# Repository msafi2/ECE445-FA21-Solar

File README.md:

# ECE445-FA21-Solar
GitHub Repository for UIUC ECE 445:Senior Design Laboratory Team in the Fall 2021 term comprised of Nikhil Mathew Sebastian (nikhils4), Sydney Li (sydneyl3), and Maram Safi (msafi2)

This repository contains all the source code for the Senior Design Lab project of this team, all relevant team project documentation, as well as team members' individual Lab Notebook entries. 

The project this team has undertaken is the **'Advanced Interface Box for Solar Panels'** project sponsored and advised for by Professor Arijit Banerjee.

## Team
1. Nikhil Mathew Sebastian [nikhils4]
2. Sydney Li [sydneyl3]
3. Maram Safi [msafi2]

## Problem
There are 60 solar panels on top of the ECEB building, currently being used for research, which are not producing any power as of now and can potentially be integrated into the power grid. Additionally, they are not adequately monitored at the moment and this poses a large hazard, especially considering there are no protection interfaces between the panels and their connections to the power inverter.

We want to design a smart interface box for these panels to allow for large-scale system behavior and output monitoring, as well as to support panel up-keep, to prevent any potential disasters like fires while also opening the possibility of future integration of these solar panels into other avenues. In previous semesters (FA19), a team of students were able to create an interface which was able to display a single panel's voltage and current, but the solution could not be scaled up to interface with multiple panels as is required. This previous solution attempt also now gives us a constrained size which we must utilize to communicate with multiple of these research solar panels.

## Solution Overview
Our solution to monitoring and maintaining the research solar panels is a smart interface box that will interface with multiple solar panels to produce a single wireless gateway of panel information that feeds into a visually attractive Research Hub for observation and access to research panel data.

The system will be powered from an isolated power supply. The power generated by each monitored solar panel will run through our smart interface box, giving us the ability to detect overvoltage and overcurrent conditions and disconnect individual panels if necessary to prevent hazardous situations. Other features of the box will include reconfigurable tapping to allow users to determine which solar panels themselves are being observed. We will also provide the possibility of manual configuration of solar panels through a wireless interface, allowing users to configure and monitor the solar panel remotely through a server/PC. Finally, LEDs will be used on the box to indicate the dynamic status of panels as well as the interface. As a fail-safe for remote management of the interface being unavailable, the configuration of the interface can also be controlled manually via onboard switches.

## Solution Components

* Switching Subsystem - Contains the ability to reconfigure which sections of the solar panel are being displayed to the wireless interface
* Manual Switches - For manual configuration of the interface box in which the wireless service access may be unavailable. The switches on the interface box can configure the solar panels and will be mounted on the enclosure. Most likely done through combinational or sequential logic depending on how much functionality we can implement
* LED Display - Displays the current status of information gathered from the panels and distinguishes whether the interface box is active or whether the wireless communication is accessible at the moment.
* Thermocouples - Measuring the temperature of the panels in a parallel manner so that a collective combination of data from different panels can be displayed.
* Microcontroller - The main processor for our interface box which has functionality such as being able to communicate the data received from the solar panels, shut down its 12V operations or limit any protection from overvoltage/current, and to determine areas in which certain panels may be overheating. Contains an electrical monitoring system to measure the voltage and current of the panels. We plan on displaying additional data beyond that which may include detailed waveforms and power calculations to our display system.
* Wireless Microchip - Utilizing a microchip to bring about wifi functionality to push data at high speeds from the interface box to the research hub
* Wireless sensor network - In order to scale up the project to have our microprocessor communicate with multiple solar panels, there needs to be a wireless node network. We cannot strictly rely on wiring which communicates one panel's information, instead having a range of sensor nodes spatially dispersed to monitor and record the conditions of each individual solar panel which help bring in collective data to our display.
* Remote Configuration Portal - An external system will be set-up with two-way communication with the box’s wireless network capabilities to allow for easy managing of the solar panels. Only authorized ECEB personnel will have access to this portal and it is intended for internal use, so the interface will be secured as such. The focus will be less the visualization of the data and more on porting the in-box button and switch capabilities to a remote setting for usage. Relevant data can be stored in a database, and a python-based framework will be able to extract and transmit commands, while JavaScript/Java can also be used to build up the framework. REST API can be utilized for the back-and-forth communication stream.
* Visual Display System - An external system that receives panel-specific data output through the Wireless Interface, and then stores the information in a database for display. Once again, a python-based framework will be able to extract, transmit commands, and display the data, while JavaScript/Java can also be used to build up the framework. REST API can also be used for receiving data. A web-based visualization of the data, with a focus on aesthetics, can then be provided for public display as well as monitoring. Both the database and the GUI will be secured to only allow authorized ECEB personnel to control the data.

## Criterion for Success

1. With a focus on scaling up to meet the requirements of the solar panels available, we need to be able to interface with at least 10 research solar panels to be successful
2. Interfacing with a solar panel successfully encompasses accurately monitoring its voltage, current, power output, and temperature while simultaneously reporting this data to an external server. (Higher functionality may include satellite imagery or different interpretations of the data received to determine the power usage during different times throughout the day.)
3. Remote Wireless Access towards the panels for the authorized ECEB personnel will be successful when it allows for these personnel to configure the solar panels from an external system
4. A successful interface will also provide a Wireless one-way communication to a visual “Hub” for scaled panel monitoring, providing aesthetic visualizations of panel data for observation as well as for general viewing
5. A successful prototype will also maintain the ability to manually control the interface box with in-box buttons and switches as a fail-safe

Our final goal is to have an easy-to-use interface supported by our smart box that allows for accurate and convenient monitoring and up-keep of multiple ECEB research solar panels. We aim to have a prototype that can easily be scaled to meet the entire requirement of available solar panels, and in the end be successfully deployed in the ECEB!

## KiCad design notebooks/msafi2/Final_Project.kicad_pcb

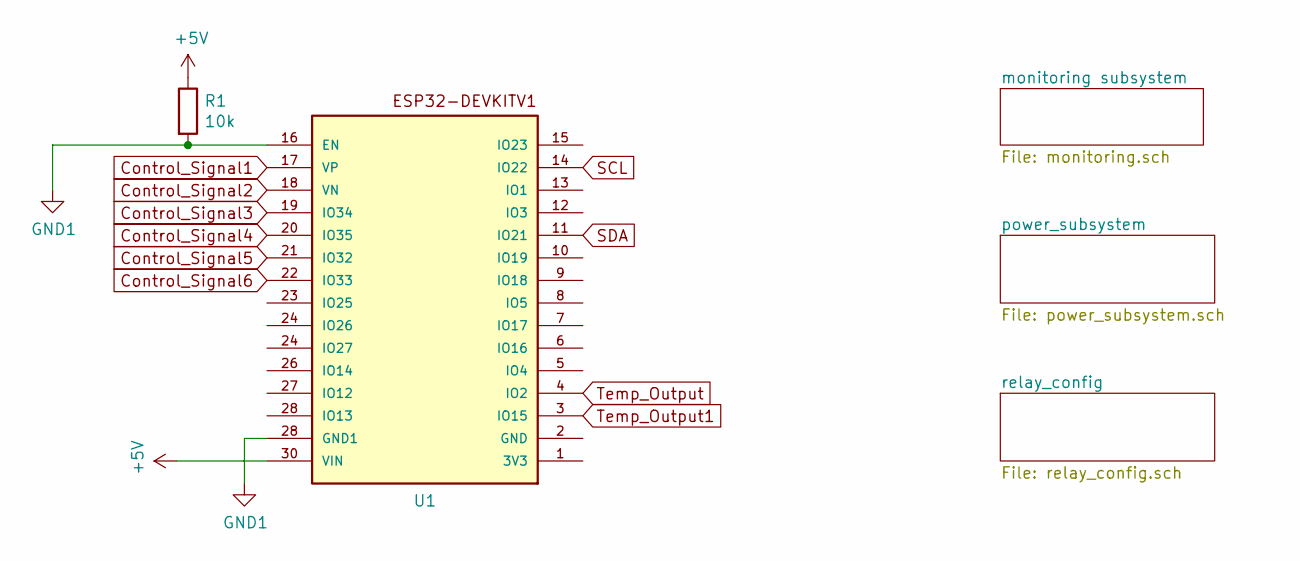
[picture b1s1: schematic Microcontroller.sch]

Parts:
R1: 10k; R_0603_1608Metric_Pad0.98x0.95mm_HandSolder
U1: ESP32DEVKITV1; ESP32-DEVKITV1

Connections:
+5V: R1.1, U1.30 (VIN); also elsewhere on the board
Control_Signal1: U1.17 (VP); also elsewhere on the board
Control_Signal2: U1.18 (VN); also elsewhere on the board
Control_Signal3: U1.19 (IO34); also elsewhere on the board
Control_Signal4: U1.20 (IO35); also elsewhere on the board
Control_Signal5: U1.21 (IO32); also elsewhere on the board
Control_Signal6: U1.22 (IO33); also elsewhere on the board
Current_output_voltage: U1.5 (IO4); also elsewhere on the board
GND1: R1.2, U1.16 (EN), U1.28 (GND1); also elsewhere on the board
SCL: U1.14 (IO22); also elsewhere on the board
SDA: U1.11 (IO21); also elsewhere on the board
Temp_Output: U1.4 (IO2); also elsewhere on the board
Temp_Output1: U1.3 (IO15); also elsewhere on the board

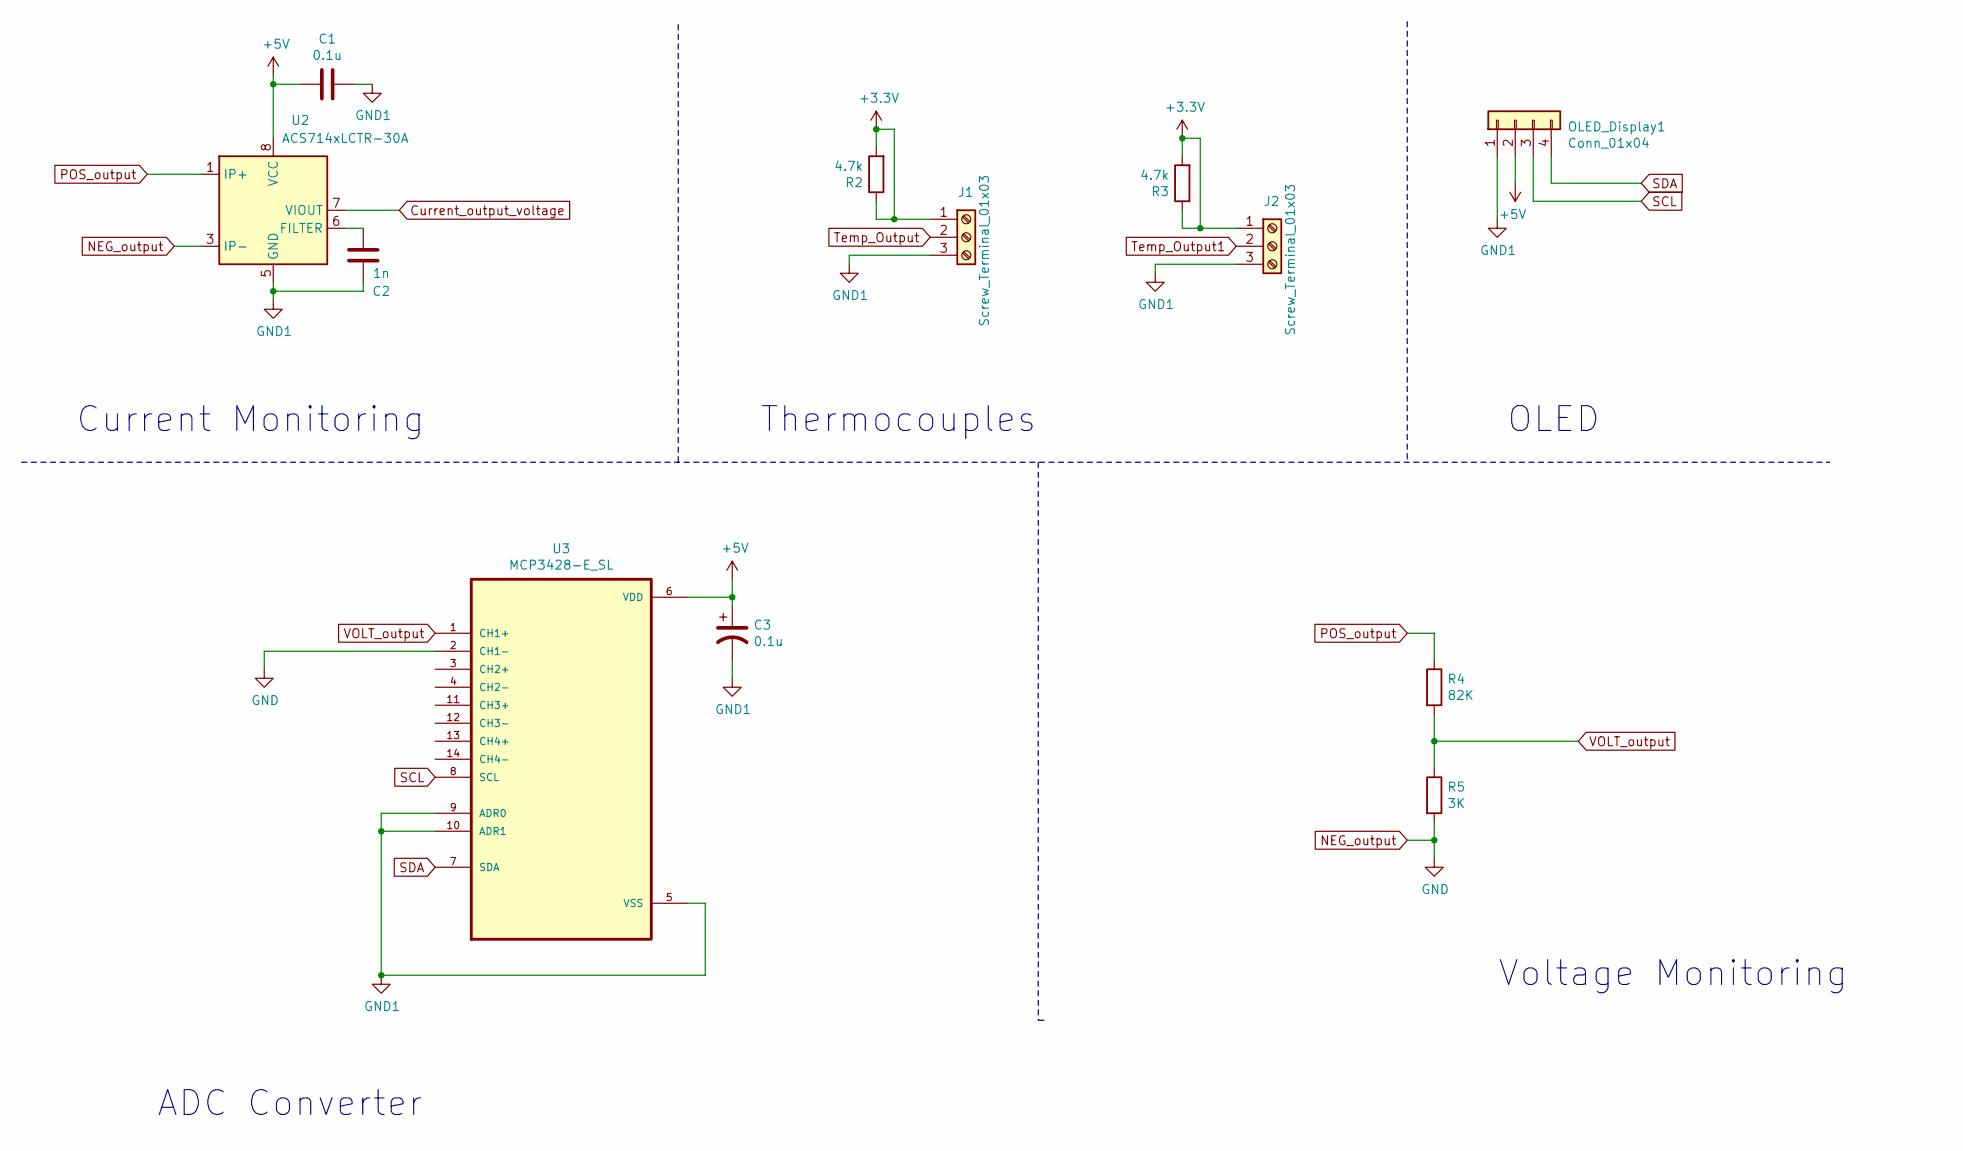
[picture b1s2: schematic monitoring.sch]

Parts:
C1, C3: 0.1u; C_0805_2012Metric_Pad1.18x1.45mm_HandSolder
C2: 1n; C_0805_2012Metric_Pad1.18x1.45mm_HandSolder
J1, J2: Screw_Terminal_01x03; 2828373
OLED_Display1: Conn_01x04; OLEDdisplay
R2, R3: 4.7k; R_0603_1608Metric_Pad0.98x0.95mm_HandSolder
R4: 82K; R_0603_1608Metric_Pad0.98x0.95mm_HandSolder
R5: 3K; R_0603_1608Metric_Pad0.98x0.95mm_HandSolder
U2: ACS714xLCTR-30A; SOIC-8_3.9x4.9mm_P1.27mm
U3: MCP3428-E_SL; SOIC127P600X175-14N

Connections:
+3V3: J1.1, J2.1, R2.1, R2.2, R3.1, R3.2; also elsewhere on the board
+5V: C1.2, C3.1, OLED_Display1.2, U2.8 (VCC), U3.6 (VDD); also elsewhere on the board
Current_output_voltage: U2.7 (VIOUT); also elsewhere on the board
GND1: C1.1, C2.1, C3.2, J1.3, J2.3, OLED_Display1.1, U2.5 (GND), U3.5 (VSS), U3.9 (ADR0), U3.10 (ADR1); also elsewhere on the board
unnamed: C2.2, U2.6 (FILTER)
POS_output: R4.1, U2.1 (IP+), U2.2 (IP+); also elsewhere on the board
SCL: OLED_Display1.3, U3.8 (SCL); also elsewhere on the board
SDA: OLED_Display1.4, U3.7 (SDA); also elsewhere on the board
Temp_Output: J1.2; also elsewhere on the board
Temp_Output1: J2.2; also elsewhere on the board
VOLT_output: R4.2, R5.1, U3.1 (CH1+)

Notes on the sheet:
Current Monitoring
Thermocouples
OLED
ADC Converter
Voltage Monitoring

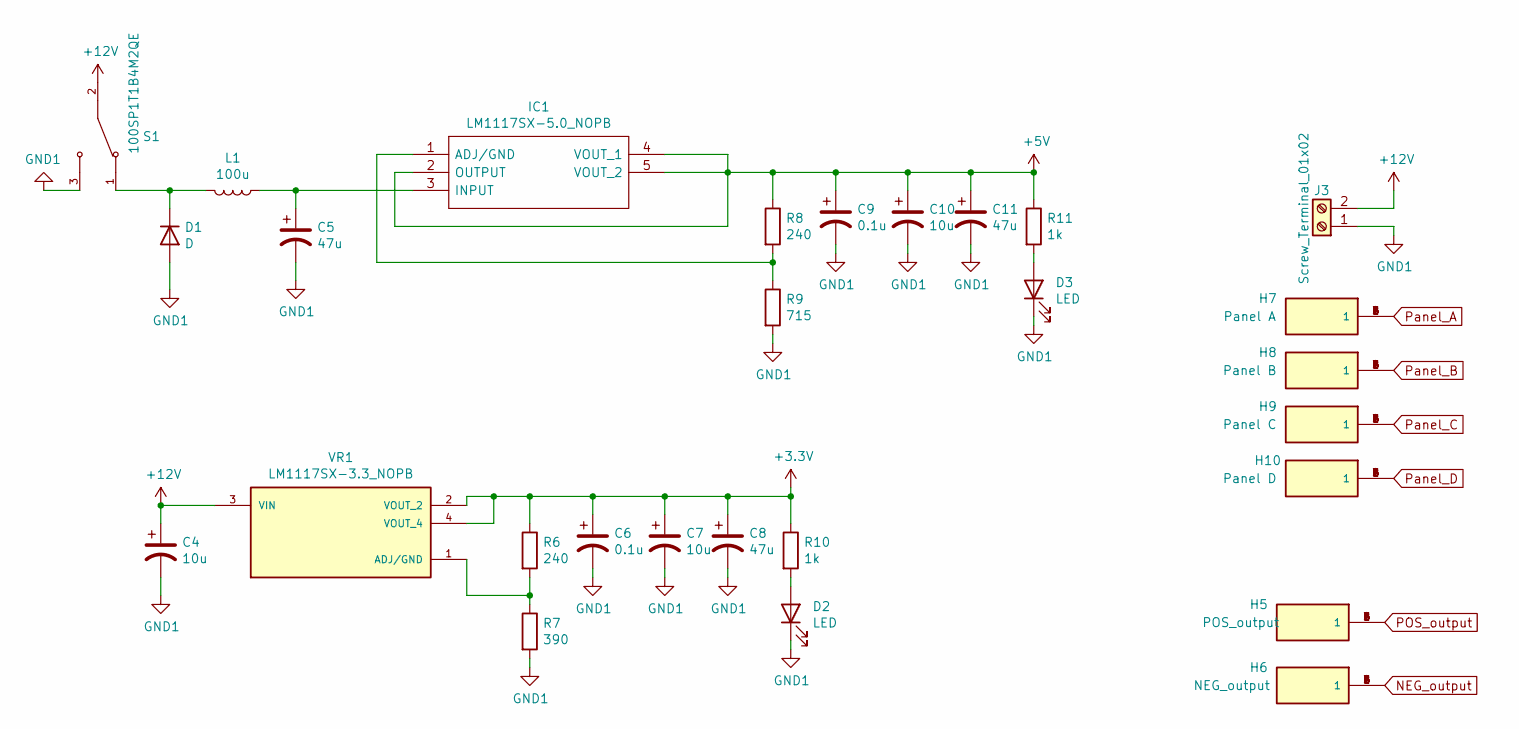
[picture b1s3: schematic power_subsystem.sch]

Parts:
C4, C7, C10: 10u; C_0805_2012Metric_Pad1.18x1.45mm_HandSolder
C5, C8, C11: 47u; CP_Elec_6.3x5.8
C6, C9: 0.1u; C_0805_2012Metric_Pad1.18x1.45mm_HandSolder
D1: D; D_0603_1608Metric_Pad1.05x0.95mm_HandSolder
D2, D3: LED; D_0603_1608Metric_Pad1.05x0.95mm_HandSolder
H5: POS_output; KEYSTONE_8197; PARTREV C
H6: NEG_output; KEYSTONE_8197; PARTREV C
H7: Panel A; KEYSTONE_8197; PARTREV C
H8: Panel B; KEYSTONE_8197; PARTREV C
H9: Panel C; KEYSTONE_8197; PARTREV C
H10: Panel D; KEYSTONE_8197; PARTREV C
IC1: LM1117SX-5.0_NOPB; LM1117SX50NOPB; Manufacturer_Part_Number LM1117SX-5.0/NOPB; Mouser Part Number 926-LM1117SX50NOPB
J3: Screw_Terminal_01x02; 2828372
L1: 100u; L_0603_1608Metric_Pad1.05x0.95mm_HandSolder
R6, R8: 240; R_0603_1608Metric_Pad0.98x0.95mm_HandSolder
R7: 390; R_0603_1608Metric_Pad0.98x0.95mm_HandSolder
R9: 715; R_0603_1608Metric_Pad0.98x0.95mm_HandSolder
R10, R11: 1k; R_0603_1608Metric_Pad0.98x0.95mm_HandSolder
S1: 100SP1T1B4M2QE; SW_100SP1T1B4M2QE; PARTREV E
VR1: LM1117SX-3.3_NOPB; TO254P1435X464-4N; PARTREV O

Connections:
+3V3: C6.1, C7.1, C8.1, R6.1, R10.1, VR1.2 (VOUT_2), VR1.4 (VOUT_4); also elsewhere on the board
+5V: C9.1, C10.1, C11.1, IC1.2 (OUTPUT), IC1.4 (VOUT_1), IC1.5 (VOUT_2), R8.1, R11.1; also elsewhere on the board
+12V: C4.1, J3.2, S1.2, VR1.3 (VIN)
GND1: C4.2, C5.2, C6.2, C7.2, C8.2, C9.2, C10.2, C11.2, D1.2 (A), D2.1 (K), D3.1 (K), J3.1, R7.2, R9.2, S1.3; also elsewhere on the board
unnamed: C5.1, IC1.3 (INPUT), L1.1
unnamed: D1.1 (K), L1.2, S1.1
unnamed: D2.2 (A), R10.2
unnamed: D3.2 (A), R11.2
unnamed: IC1.1 (ADJ/GND), R8.2, R9.1
unnamed: R6.2, R7.1, VR1.1 (ADJ/GND)
POS_output: H5.1, H5.2, H5.3, H5.4, H5.5, H5.6; also elsewhere on the board
Panel_A: H7.1, H7.2, H7.3, H7.4, H7.5, H7.6; also elsewhere on the board
Panel_B: H8.1, H8.2, H8.3, H8.4, H8.5, H8.6; also elsewhere on the board
Panel_C: H9.1, H9.2, H9.3, H9.4, H9.5, H9.6; also elsewhere on the board
Panel_D: H10.1, H10.2, H10.3, H10.4, H10.5, H10.6; also elsewhere on the board

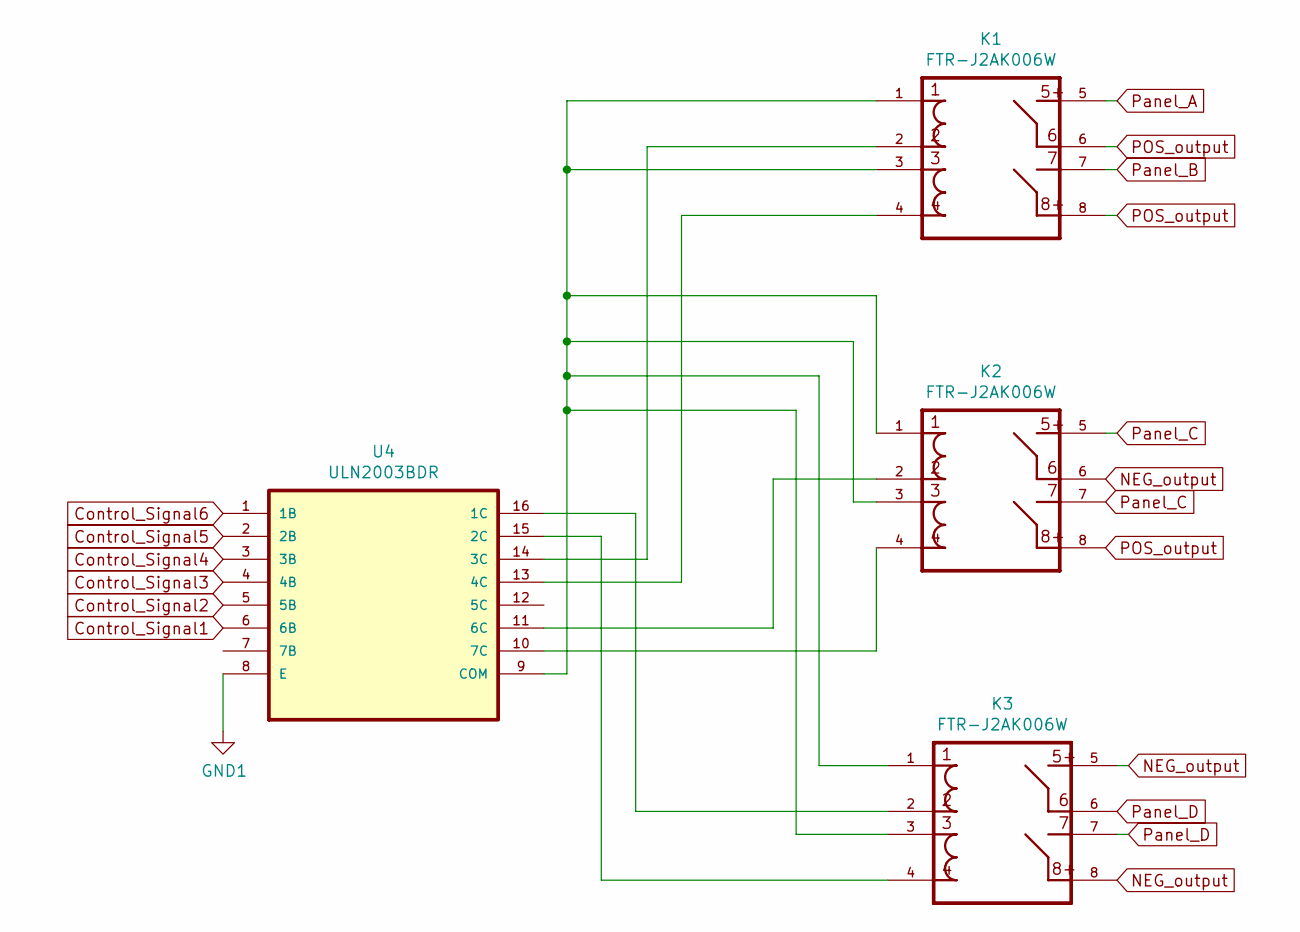
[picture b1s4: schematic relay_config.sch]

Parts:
K1, K2, K3: FTR-J2AK006W; RELAY_FTR-J2AK006W
U4: ULN2003BDR; SOIC127P600X175-16N

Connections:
Control_Signal1: U4.6 (6B); also elsewhere on the board
Control_Signal2: U4.5 (5B); also elsewhere on the board
Control_Signal3: U4.4 (4B); also elsewhere on the board
Control_Signal4: U4.3 (3B); also elsewhere on the board
Control_Signal5: U4.2 (2B); also elsewhere on the board
Control_Signal6: U4.1 (1B); also elsewhere on the board
GND1: U4.8 (E); also elsewhere on the board
unnamed: K1.1, K1.3, K2.1, K2.3, K3.1, K3.3, U4.9 (COM)
unnamed: K1.2, U4.14 (3C)
unnamed: K1.4, U4.13 (4C)
unnamed: K2.2, U4.11 (6C)
unnamed: K2.4, U4.10 (7C)
unnamed: K3.2, U4.16 (1C)
unnamed: K3.4, U4.15 (2C)
POS_output: K1.6, K1.8, K2.8; also elsewhere on the board
Panel_A: K1.5; also elsewhere on the board
Panel_B: K1.7; also elsewhere on the board
Panel_C: K2.5, K2.7; also elsewhere on the board
Panel_D: K3.6, K3.7; also elsewhere on the board

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
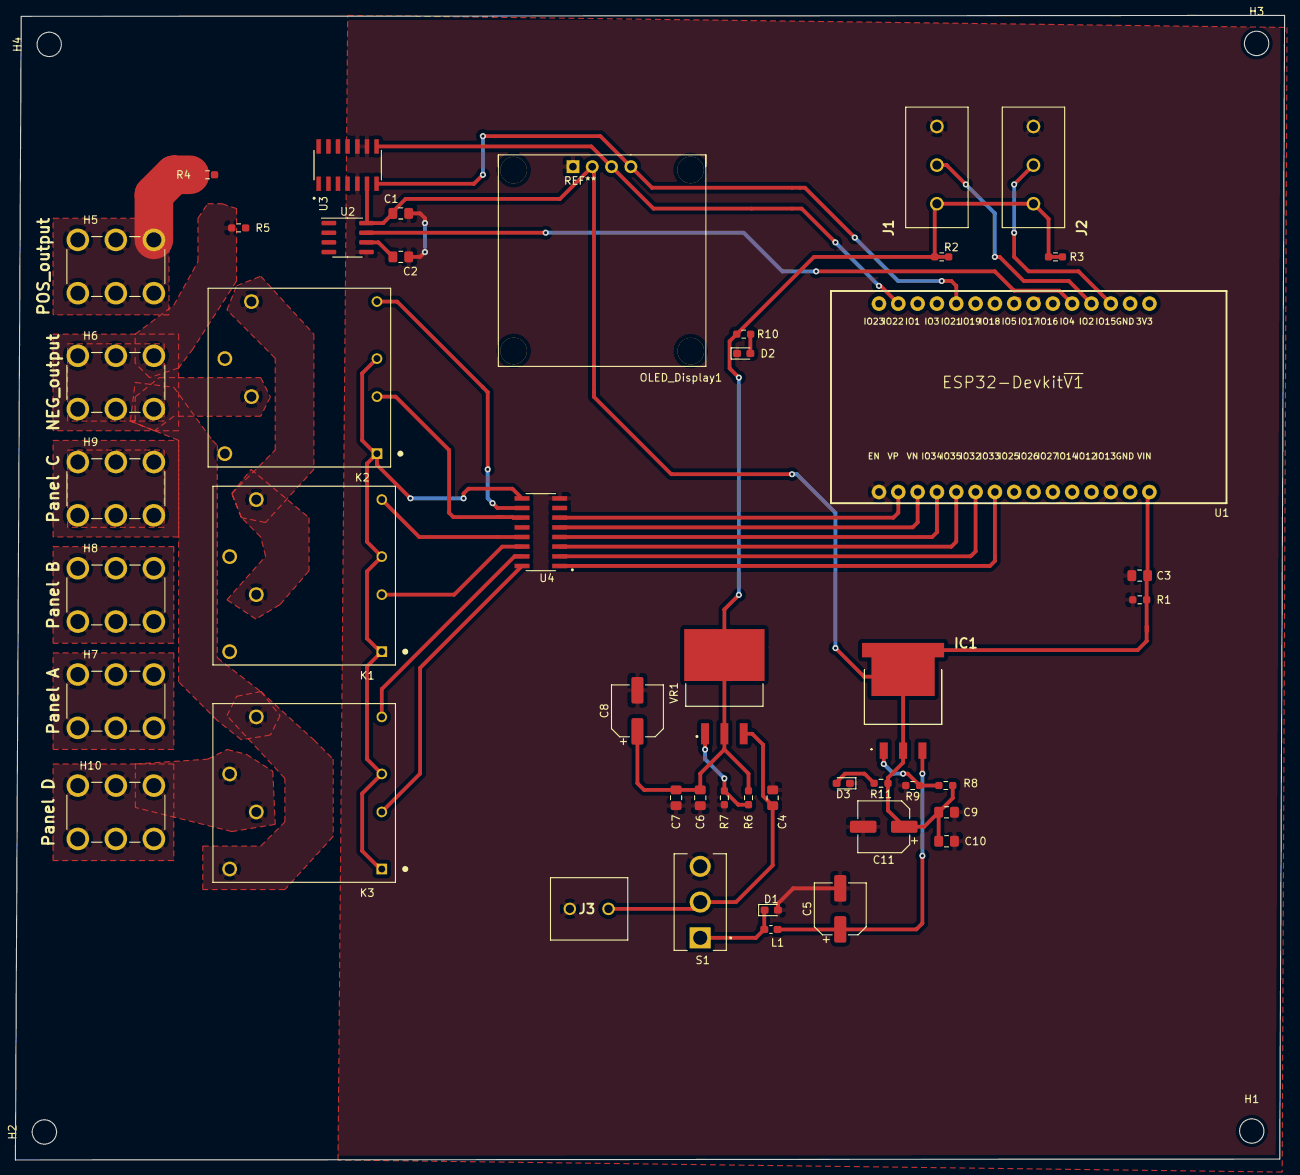
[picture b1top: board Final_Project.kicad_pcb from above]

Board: 2 copper layers, 166.9 x 150.5 mm, 50 parts (0 on the bottom side), 36 nets.

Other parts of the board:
H1, H2, H3, H4: MountingHole; MountingHole_3.2mm_M3

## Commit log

2021-09-14 Initial Update to README
2021-09-14 Setting up Lab Notebook folders
2021-09-14 Updating High-Level Project Details
2021-09-14 Creating 'src' folder for source code
2021-09-14 Removing accidental file
2021-09-14 Creating src folder for source code
2021-09-14 Create Block Diagram Draft
2021-09-14 Add files via upload
    Block Diagram (Draft #1)
2021-09-14 Create Design Structure
2021-09-14 Update Design Structure
2021-09-14 Copying work notes into personal notebook (#1)
2021-09-17 Create Examining Microcontrollers
2021-09-18 Update Examining Microcontrollers
2021-09-19 Updating entries till 09/18/2021 (Part 1)
2021-09-19 Updating entries till 09/18/2021 (Part 2)
2021-09-19 Updating notebook as of 09/18/2021
2021-09-20 Updating entries till 09/18/2021 (Part 4)
2021-09-20 Consolidating all project documents in github
2021-09-20 Updating RFA that was submitted for the team
2021-09-20 Completed updating Lab Notebook as of 09/18/2021
2021-09-20 Addition/Correction to main repo README
2021-09-25 Create PCB Design
2021-09-26 Create Cost Analysis
2021-10-05 Updating repo with latest design doc
2021-10-05 Updating Lab Notebook entries till 10/05 (Part 1)
2021-10-05 Updating current schematic draft in team documents
2021-10-09 Create Research
2021-10-11 Create Decoder Operation
    Pinout ESP32
2021-10-19 Create Testing
2021-10-19 Update Testing
2021-10-19 Completely updating Notebook entries
2021-10-26 Create KiCAD Schematics & PCB
2021-10-26 Updating Notebook Entries till 10/23
2021-10-27 Create msafi2
2021-10-27 Create test
2021-10-27 PCB Configuration Upload
